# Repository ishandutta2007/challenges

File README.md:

Various solutions to challenges

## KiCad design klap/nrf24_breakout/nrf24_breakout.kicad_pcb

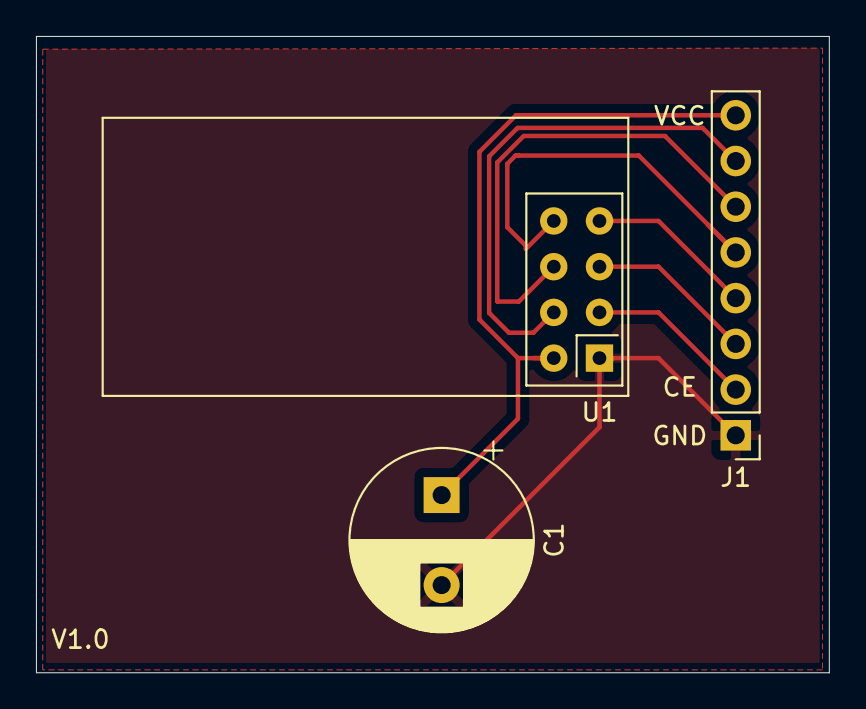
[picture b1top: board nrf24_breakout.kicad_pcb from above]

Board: 2 copper layers, 44.1 x 35.3 mm, 3 parts (0 on the bottom side), 8 nets.

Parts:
C1: CP1; CP_Radial_D10.0mm_P5.00mm
J1: Conn_01x08; PinHeader_1x08_P2.54mm_Vertical
U1: NRF24L01_Breakout; nRF24L01_Breakout

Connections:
GND: C1.2, J1.1, U1.1
unnamed: J1.2, U1.3
unnamed: J1.3, U1.5
unnamed: J1.4, U1.7
unnamed: J1.5, U1.8
unnamed: J1.6, U1.6
unnamed: J1.7, U1.4
VCC: C1.1, J1.8, U1.2

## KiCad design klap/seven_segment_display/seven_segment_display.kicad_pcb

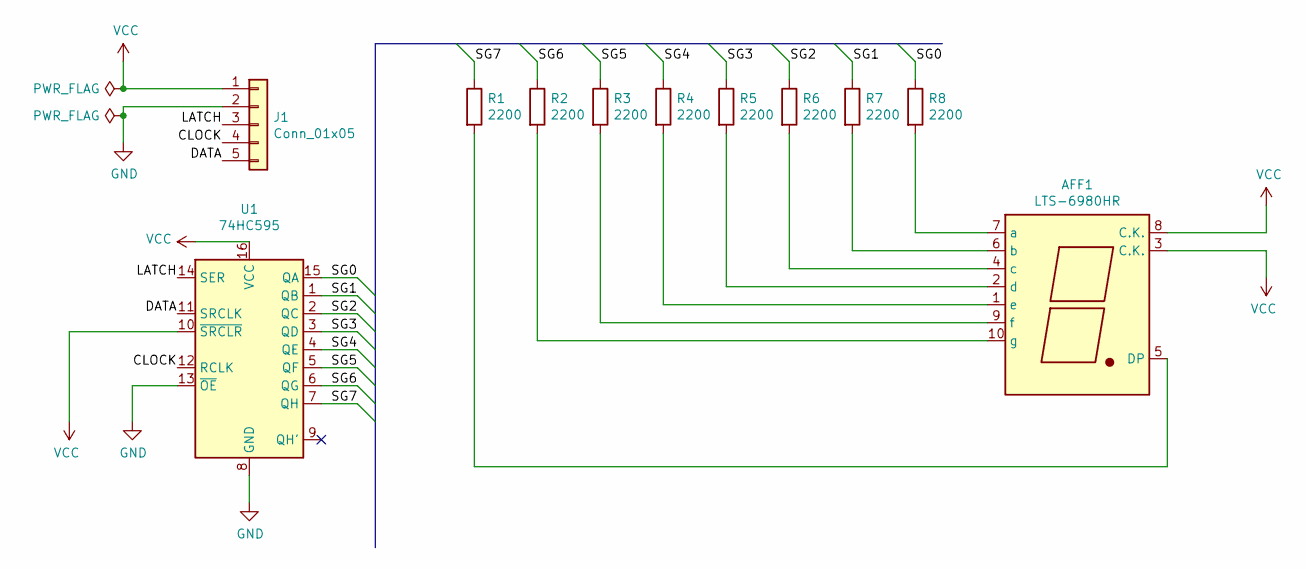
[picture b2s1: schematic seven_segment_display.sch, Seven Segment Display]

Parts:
AFF1: LTS-6980HR; 7SegmentLED_LTS6760_LTS6780
J1: Conn_01x05; PinHeader_1x05_P2.54mm_Horizontal
R1, R2, R3, R4, R5, R6, R7, R8: 2200; R_Axial_DIN0411_L9.9mm_D3.6mm_P25.40mm_Horizontal
U1: 74HC595; DIP16-2.54-20.32X5.84MM

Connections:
/CLOCK: J1.4, U1.12 (RCLK)
/DATA: J1.5, U1.11 (SRCLK)
/LATCH: J1.3, U1.14 (SER)
/SG0: R8.1, U1.15 (QA)
/SG1: R7.1, U1.1 (QB)
/SG2: R6.1, U1.2 (QC)
/SG3: R5.1, U1.3 (QD)
/SG4: R4.1, U1.4 (QE)
/SG5: R3.1, U1.5 (QF)
/SG6: R2.1, U1.6 (QG)
/SG7: R1.1, U1.7 (QH)
GND: J1.2, U1.8 (GND), U1.13 (~OE)
unnamed: AFF1.1 (e), R4.2
unnamed: AFF1.2 (d), R5.2
unnamed: AFF1.4 (c), R6.2
unnamed: AFF1.5 (DP), R1.2
unnamed: AFF1.6 (b), R7.2
unnamed: AFF1.7 (a), R8.2
unnamed: AFF1.9 (f), R3.2
unnamed: AFF1.10 (g), R2.2
VCC: AFF1.3 (C.K.), AFF1.8 (C.K.), J1.1, U1.10 (~SRCLR), U1.16 (VCC)

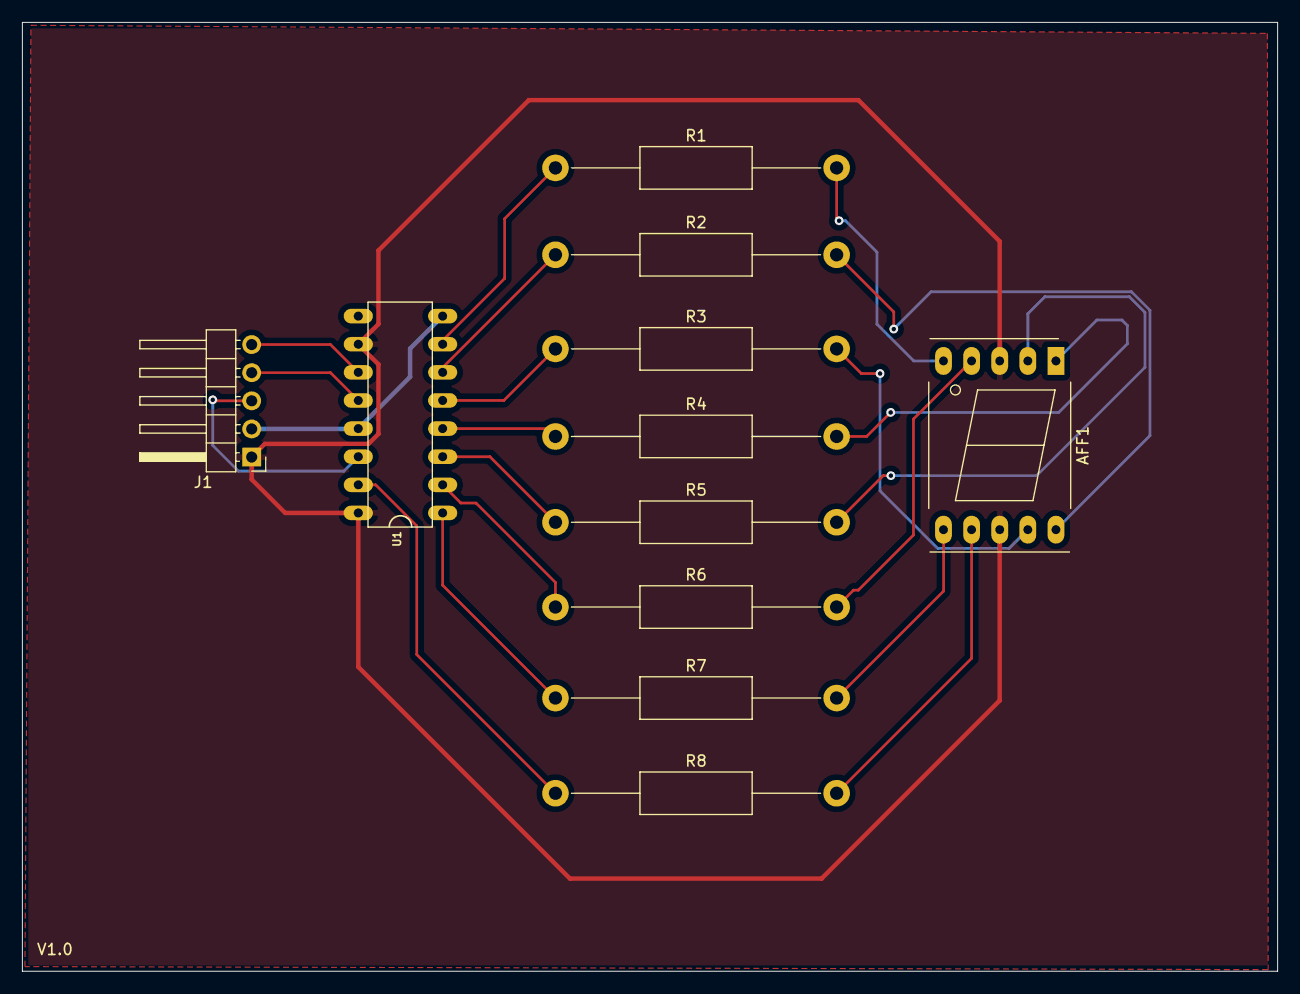
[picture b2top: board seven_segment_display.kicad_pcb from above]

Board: 2 copper layers, 113.4 x 85.7 mm, 11 parts (0 on the bottom side), 21 nets.

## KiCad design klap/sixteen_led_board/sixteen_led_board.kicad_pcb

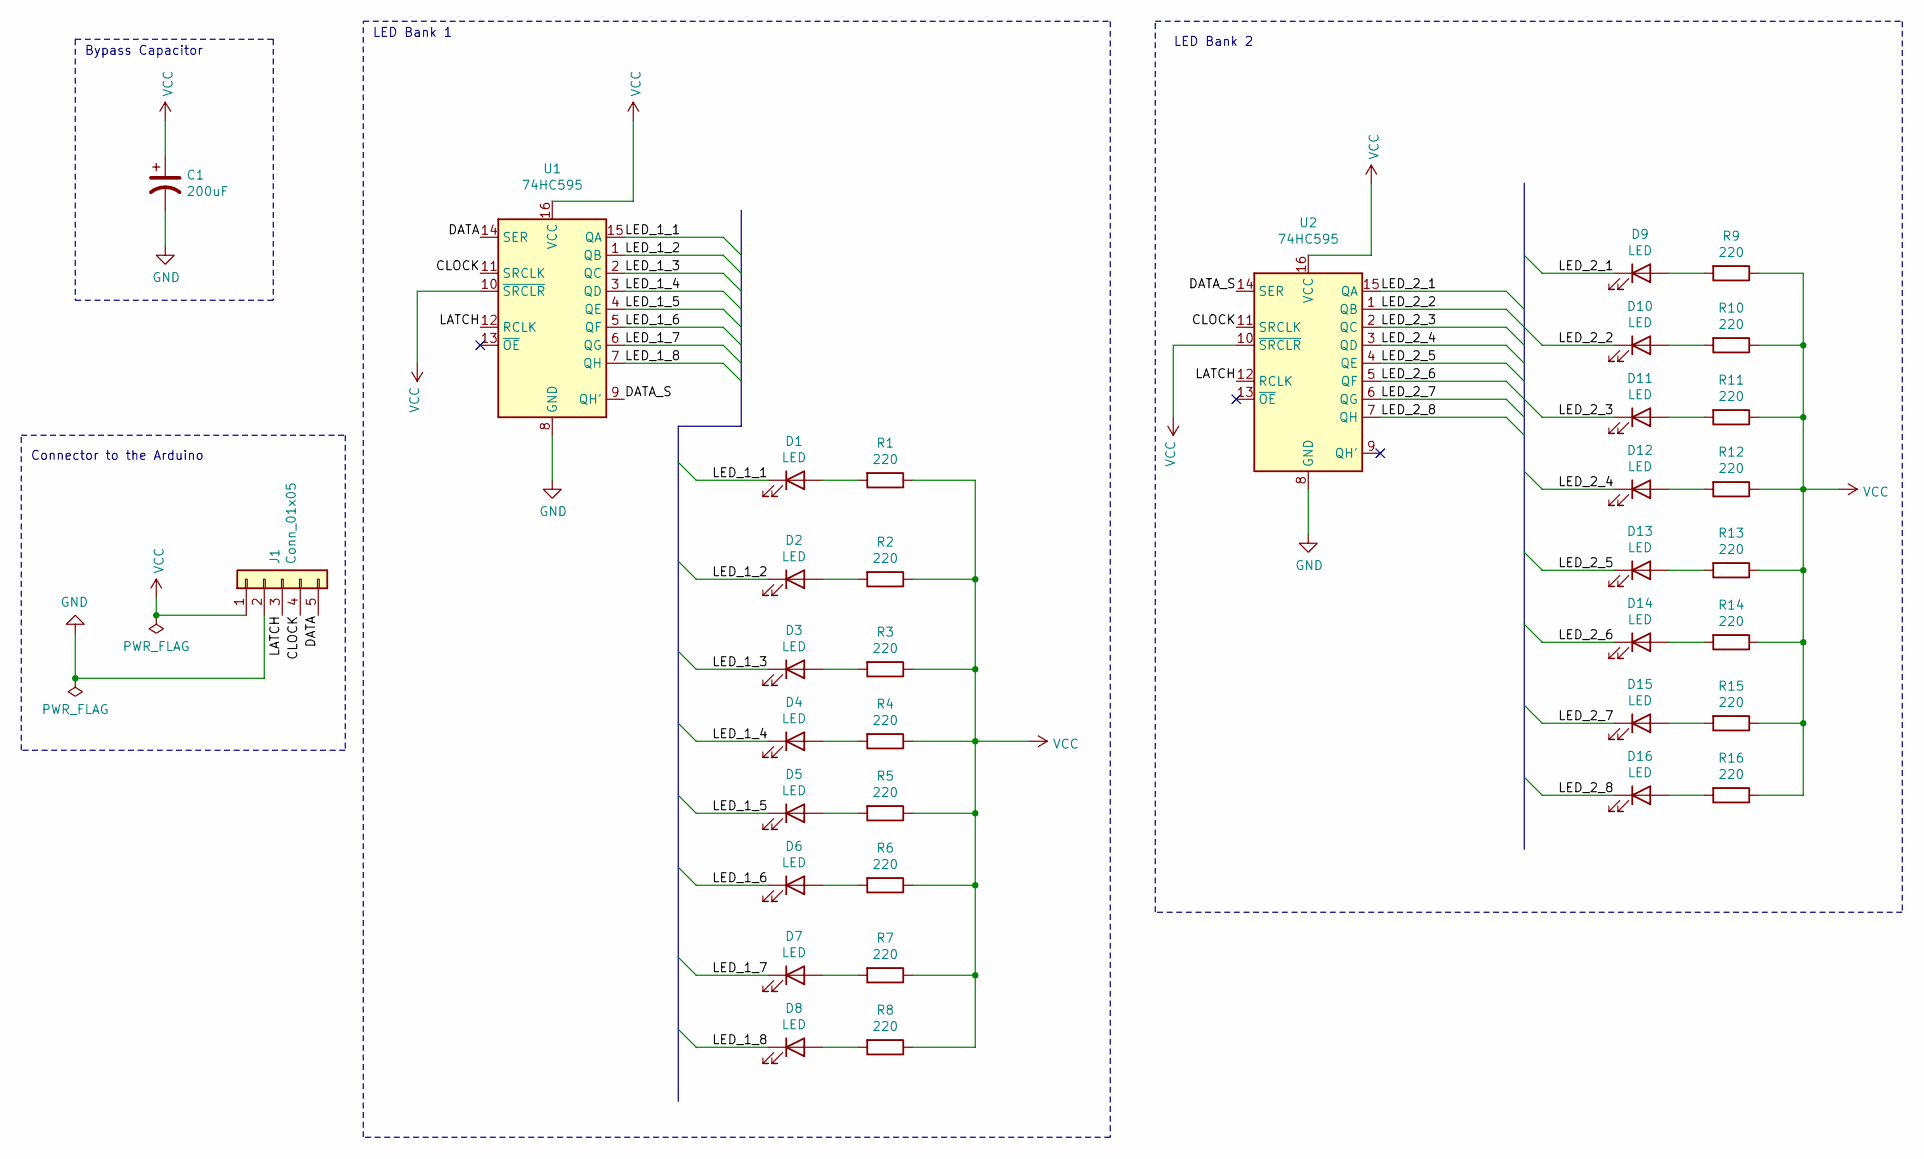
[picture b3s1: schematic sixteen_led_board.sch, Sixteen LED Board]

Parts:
C1: 200uF; CP_Elec_6.3x5.3
D1, D2, D3, D4, D5, D6, D7, D8, D9, D10, D11, D12, D13, D14, D15, D16: LED; LED_0805_2012Metric
J1: Conn_01x05; PinHeader_1x05_P2.54mm_Vertical_SMD_Pin1Left
R1, R2, R3, R4, R5, R6, R7, R8, R9, R10, R11, R12, R13, R14, R15, R16: 220; R_0805_2012Metric_Pad1.20x1.40mm_HandSolder
U1, U2: 74HC595; SO16

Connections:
/CLOCK: J1.4, U1.11 (SRCLK), U2.11 (SRCLK)
/DATA: J1.5, U1.14 (SER)
/DATA_S: U1.9 (QH'), U2.14 (SER)
/LATCH: J1.3, U1.12 (RCLK), U2.12 (RCLK)
/LED_1_1: D1.1 (K), U1.15 (QA)
/LED_1_2: D2.1 (K), U1.1 (QB)
/LED_1_3: D3.1 (K), U1.2 (QC)
/LED_1_4: D4.1 (K), U1.3 (QD)
/LED_1_5: D5.1 (K), U1.4 (QE)
/LED_1_6: D6.1 (K), U1.5 (QF)
/LED_1_7: D7.1 (K), U1.6 (QG)
/LED_1_8: D8.1 (K), U1.7 (QH)
/LED_2_1: D9.1 (K), U2.15 (QA)
/LED_2_2: D10.1 (K), U2.1 (QB)
/LED_2_3: D11.1 (K), U2.2 (QC)
/LED_2_4: D12.1 (K), U2.3 (QD)
/LED_2_5: D13.1 (K), U2.4 (QE)
/LED_2_6: D14.1 (K), U2.5 (QF)
/LED_2_7: D15.1 (K), U2.6 (QG)
/LED_2_8: D16.1 (K), U2.7 (QH)
GND: C1.2, J1.2, U1.8 (GND), U2.8 (GND)
unnamed: D1.2 (A), R1.2
unnamed: D2.2 (A), R2.2
unnamed: D3.2 (A), R3.2
unnamed: D4.2 (A), R4.2
unnamed: D5.2 (A), R5.2
unnamed: D6.2 (A), R6.2
unnamed: D7.2 (A), R7.2
unnamed: D8.2 (A), R8.2
unnamed: D9.2 (A), R9.2
unnamed: D10.2 (A), R10.2
unnamed: D11.2 (A), R11.2
unnamed: D12.2 (A), R12.2
unnamed: D13.2 (A), R13.2
unnamed: D14.2 (A), R14.2
unnamed: D15.2 (A), R15.2
unnamed: D16.2 (A), R16.2
VCC: C1.1, J1.1, R1.1, R2.1, R3.1, R4.1, R5.1, R6.1, R7.1, R8.1, R9.1, R10.1, R11.1, R12.1, R13.1, R14.1, R15.1, R16.1, U1.10 (~SRCLR), U1.16 (VCC), U2.10 (~SRCLR), U2.16 (VCC)

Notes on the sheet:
Bypass Capacitor
LED Bank 1
Connector to the Arduino
LED Bank 2

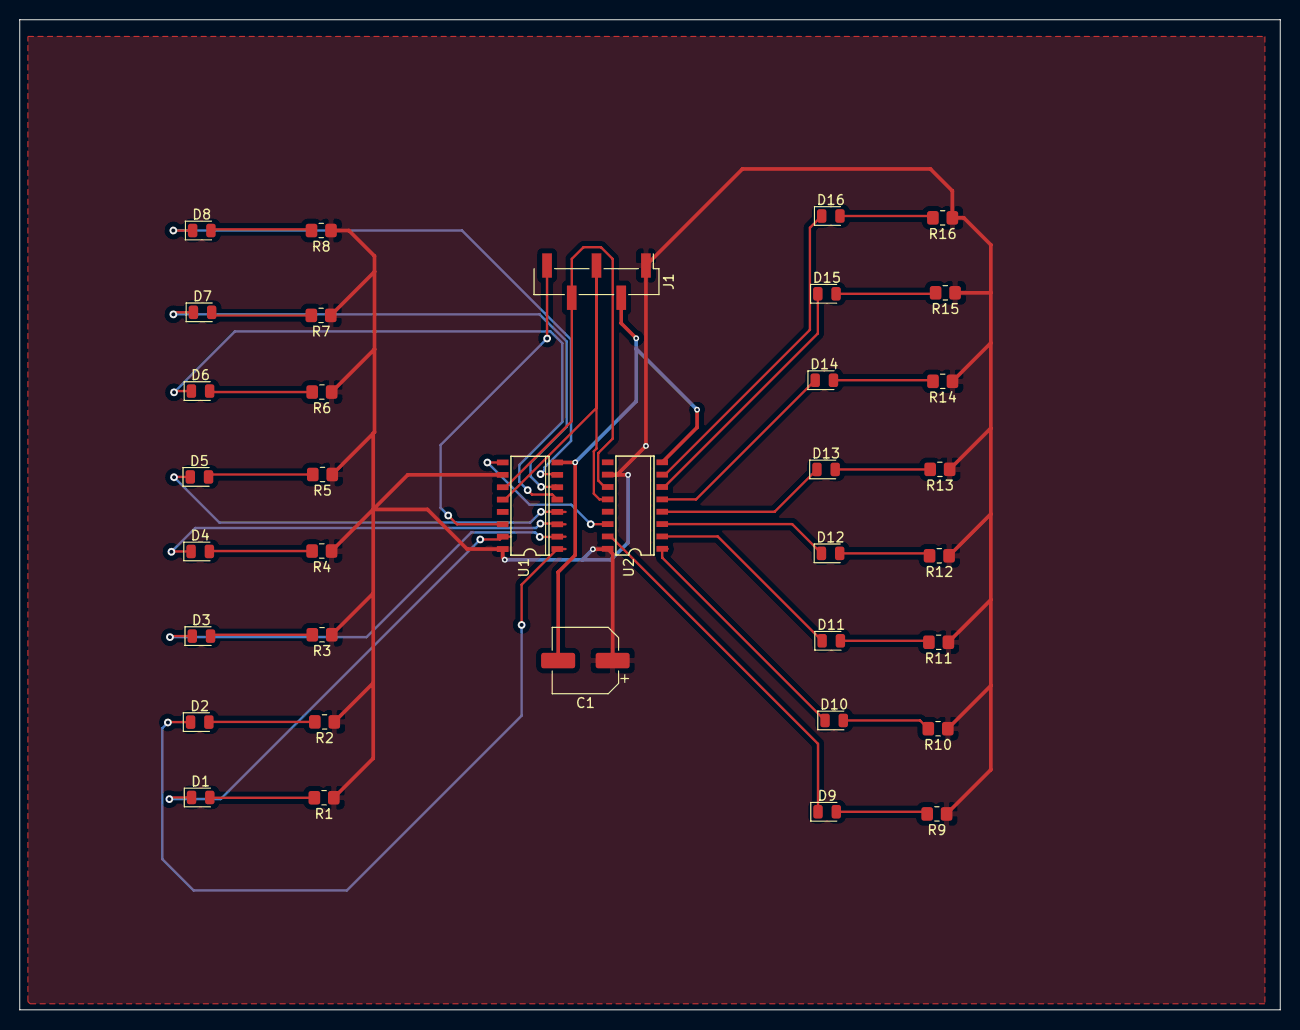
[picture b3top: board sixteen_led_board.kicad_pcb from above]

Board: 2 copper layers, 129.5 x 101.7 mm, 36 parts (0 on the bottom side), 38 nets.

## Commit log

2022-10-30 initial
